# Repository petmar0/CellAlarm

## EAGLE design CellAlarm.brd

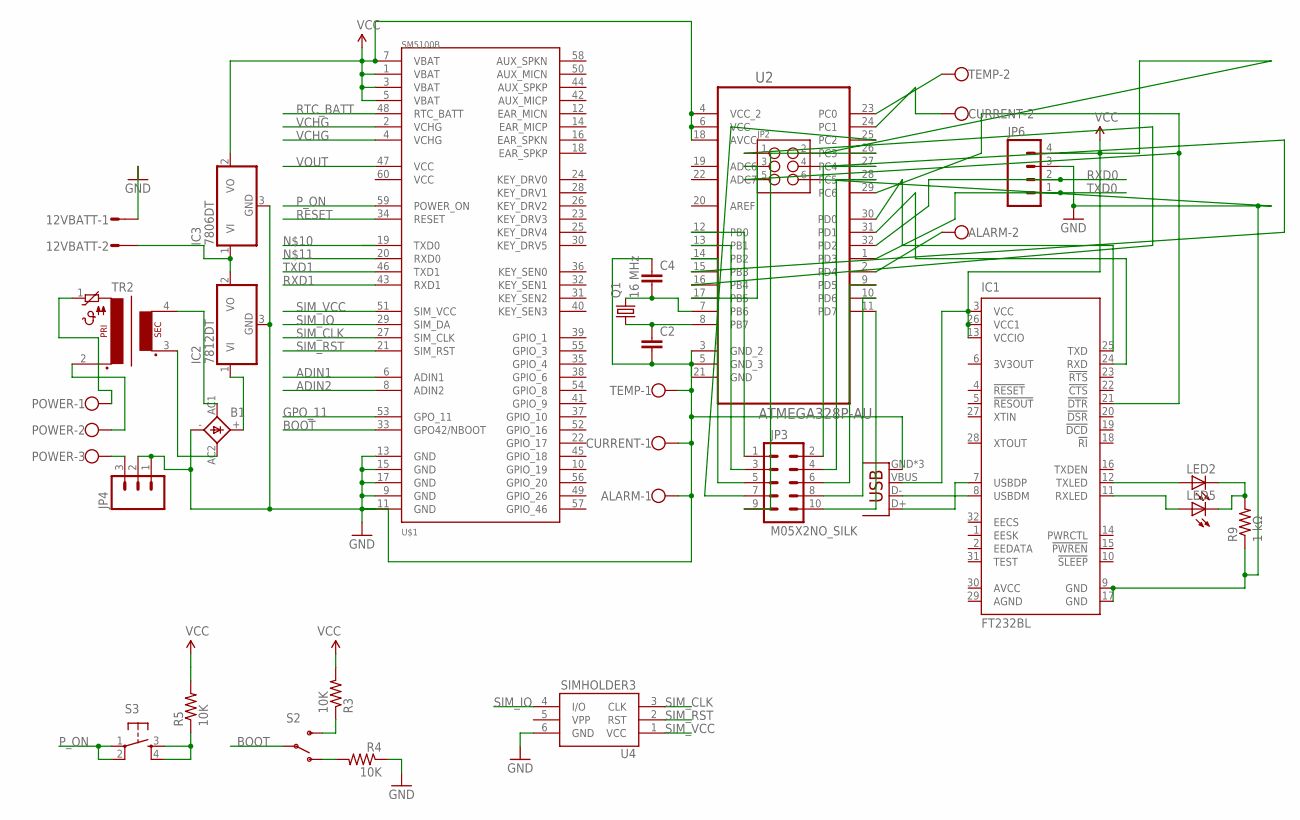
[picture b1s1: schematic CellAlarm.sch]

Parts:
12VBATT: M02S; 02P
ALARM: W239-302
B1: 2KBB-R
C2, C4: C2.5/2; C2.5-2
CURRENT: W239-302
IC1: FT232BL; LQFP32-7X7
IC2: 7812DT; TO252
IC3: 7806DT; TO252
JP1: USB-MICROB
JP2: M03X2NO_SILK; 2X3-NS
JP3: M05X2NO_SILK; 2X5_NOSILK
JP4: M03LONGPADS; 1X03_LONGPADS
JP6: M04PTH; 1X04
LED2, LED5: LED_E; LED_1206
POWER: W239-103
Q1: 16 MHz; HC33U-V
R3, R4, R5: 10K; R0603
R9: 1 kΩ; M0805
S2: SWITCH-SPSTSMD; AYZ0202
S3: TAC_SWITCHSMD; TACTILE_SWITCH_SMD
TEMP: W239-302
TR2: PT04,5-1
U2: ATMEGA328P-AU; QFP80P900X900X120-32N
U4: SIMHOLDER3
U$1: SM5100B

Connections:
ADIN1: U$1.6 (ADIN1)
ADIN2: U$1.8 (ADIN2)
AGND: IC1.29 (AGND)
AVCC: IC1.30 (AVCC)
BOOT: S2.2, U$1.33 (GPO42/NBOOT)
GND: 12VBATT.1, ALARM.1, B1.-, C2.2, C4.1, CURRENT.1, IC1.9 (GND), IC1.17 (GND), IC2.3 (GND), IC3.3 (GND), JP1.GND, JP1.MT1 (GND), JP1.MT2 (GND), JP2.6, JP4.1, JP4.2, JP6.3, R4.1, R9.1, TEMP.1, U2.3 (GND_2), U2.5 (GND_3), U2.21 (GND), U4.6 (GND), U$1.9 (GND), U$1.11 (GND), U$1.13 (GND), U$1.15 (GND), U$1.17 (GND)
GPO_11: U$1.53 (GPO_11)
unnamed: POWER.1, TR2.1
unnamed: POWER.2, TR2.2
unnamed: B1.AC2, TR2.3
unnamed: B1.AC1, TR2.4
unnamed: IC1.12 (TXLED), LED2.A
unnamed: B1.+, IC2.1 (VI)
unnamed: 12VBATT.2, IC2.2 (VO), IC3.1 (VI)
unnamed: TEMP.2, U2.23 (PC0)
unnamed: CURRENT.2, U2.24 (PC1)
unnamed: JP4.3, POWER.3
unnamed: R3.1, S2.3 (S)
unnamed: R4.2, S2.1 (O)
unnamed: ALARM.2, U2.2 (PD4)
unnamed: R5.1, S3.3, S3.4
unnamed: IC1.11 (RXLED), LED5.A
unnamed: LED2.C, LED5.C, R9.2
unnamed: IC1.7 (USBDP), JP1.D+
unnamed: IC1.8 (USBDM), JP1.D-
unnamed: IC1.25 (TXD), U2.30 (PD0)
unnamed: IC1.24 (RXD), U2.31 (PD1)
unnamed: IC1.21 (!DTR), JP2.5, U2.29 (PC6)
unnamed: JP2.4, U2.15 (PB3)
unnamed: JP2.1, U2.16 (PB4)
unnamed: JP2.3, U2.17 (PB5)
unnamed: C4.2, Q1.2, U2.7 (PB6)
unnamed: C2.1, Q1.1, U2.8 (PB7)
unnamed: JP3.1, U2.12 (PB0)
unnamed: JP3.3, U2.13 (PB1)
unnamed: JP3.5, U2.14 (PB2)
unnamed: JP3.7, U2.25 (PC2)
unnamed: JP3.9, U2.26 (PC3)
unnamed: JP3.2, U2.27 (PC4)
unnamed: JP3.4, U2.28 (PC5)
unnamed: JP3.6, U2.9 (PD5)
unnamed: JP3.8, U2.10 (PD6)
unnamed: JP3.10, U2.11 (PD7)
P_ON: S3.1, S3.2, U$1.59 (POWER_ON)
RESET: U$1.34 (RESET)
RTC_BATT: U$1.48 (RTC_BATT)
RXD0: JP6.2, U2.32 (PD2)
RXD1: U$1.43 (RXD1)
SIM_CLK: U4.3 (CLK), U$1.27 (SIM_CLK)
SIM_IO: U4.4 (I/O), U$1.29 (SIM_DA)
SIM_RST: U4.2 (RST), U$1.21 (SIM_RST)
SIM_VCC: U4.1 (VCC), U$1.51 (SIM_VCC)
TXD0: JP6.1, U2.1 (PD3)
TXD1: U$1.46 (TXD1)
VCC: IC1.3 (VCC), IC1.13 (VCCIO), IC1.26 (VCC1), IC3.2 (VO), JP1.VBUS, JP2.2, JP6.4, R3.2, R5.2, U2.4 (VCC_2), U2.6 (VCC), U2.18 (AVCC), U$1.1 (VBAT), U$1.3 (VBAT), U$1.5 (VBAT), U$1.7 (VBAT)
VCHG: U$1.2 (VCHG), U$1.4 (VCHG)
VOUT: U$1.47 (VCC)

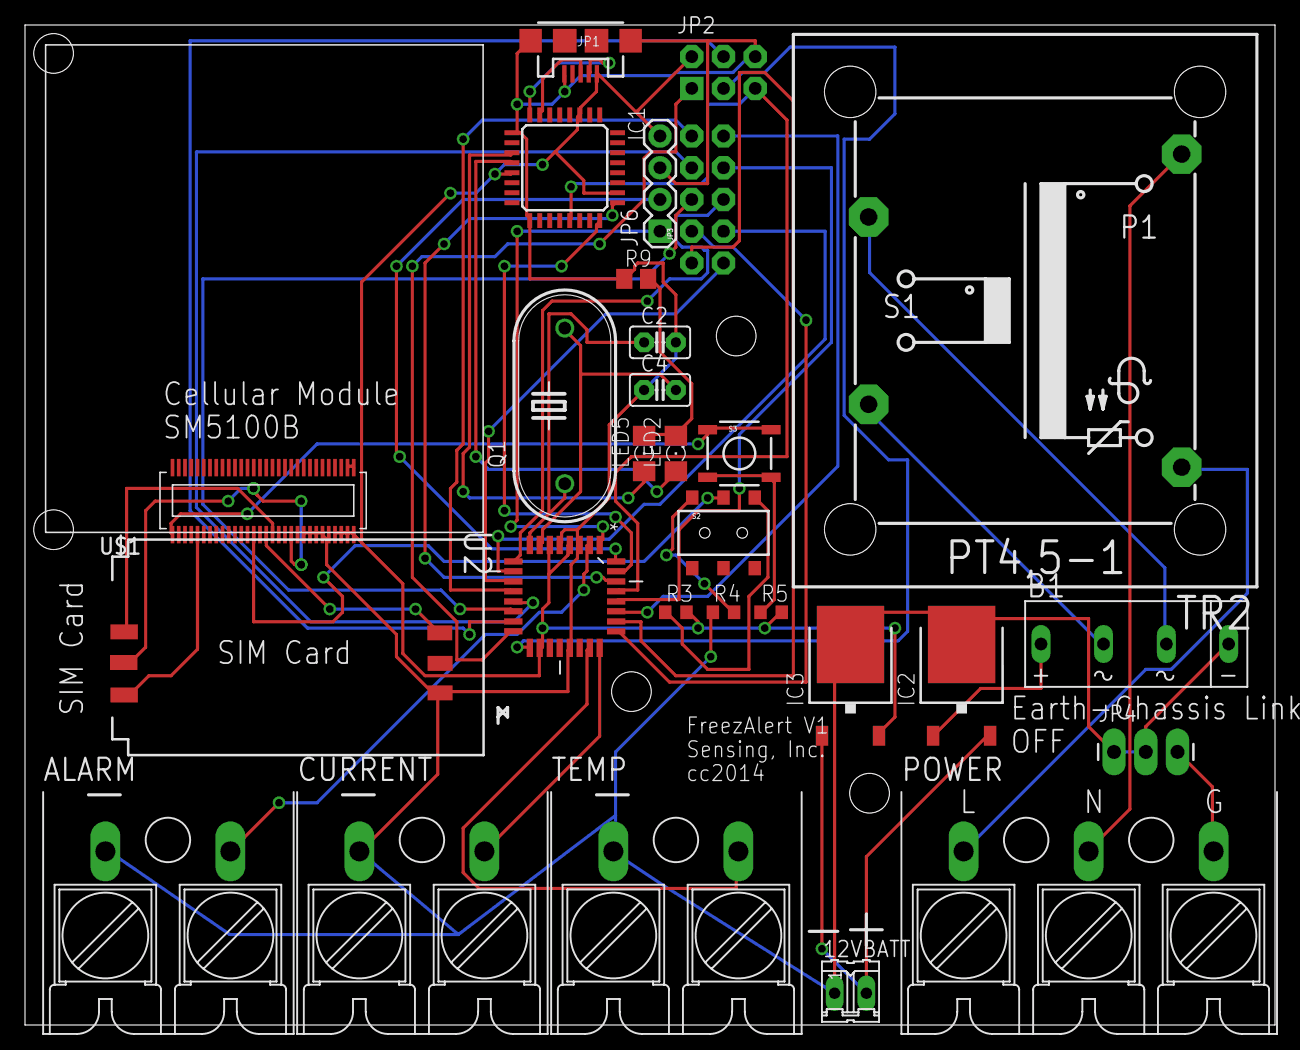
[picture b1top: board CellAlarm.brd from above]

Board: 2 copper layers, 100.0 x 80.0 mm, 29 parts (0 on the bottom side), 47 nets.

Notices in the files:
parts and their libraries:
SparkFun-Connectors: Licensing: CC v3.0 Share-Alike You are welcome to use this library for commercial purposes.
